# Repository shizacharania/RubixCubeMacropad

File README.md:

# RubixCubeMacropad

a fun project i built out over a weekend - learned how to make a PCB through kicad + made a rubix cube enclosure that has a three part assembly, with the pieces being precisely located + designed firmware for the macropad through KMK!

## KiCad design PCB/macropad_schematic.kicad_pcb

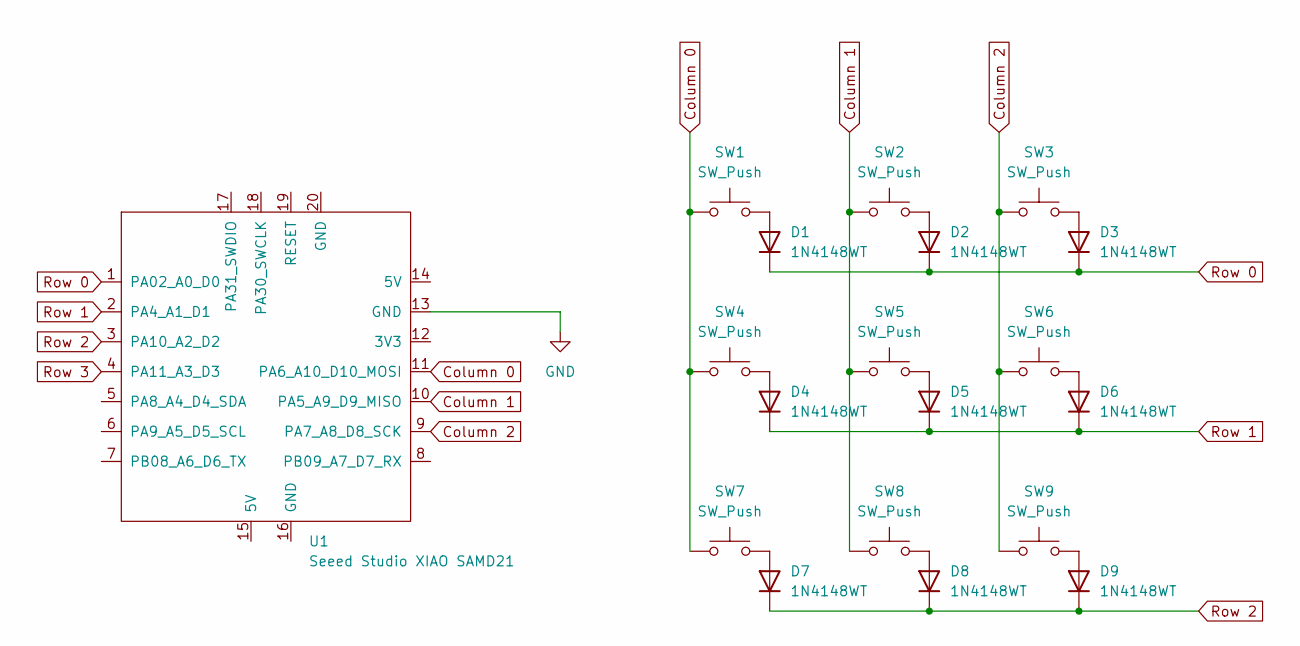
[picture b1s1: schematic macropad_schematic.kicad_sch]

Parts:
D1, D2, D3, D4, D5, D6, D7, D8, D9: 1N4148WT; D_SOD-523
SW1, SW2, SW3, SW4, SW5, SW6, SW7, SW8, SW9: SW_Push; SW_Cherry_MX_1.00u_PCB
U1: Seeed Studio XIAO SAMD21; XIAO-RP2040-SMD

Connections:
Column 0: SW1.1, SW4.1, SW7.1, U1.11 (PA6_A10_D10_MOSI)
Column 1: SW2.1, SW5.1, SW8.1, U1.10 (PA5_A9_D9_MISO)
Column 2: SW3.1, SW6.1, SW9.1, U1.9 (PA7_A8_D8_SCK)
GND: U1.13 (GND)
unnamed: D1.2 (A), SW1.2
unnamed: D2.2 (A), SW2.2
unnamed: D3.2 (A), SW3.2
unnamed: D4.2 (A), SW4.2
unnamed: D5.2 (A), SW5.2
unnamed: D6.2 (A), SW6.2
unnamed: D7.2 (A), SW7.2
unnamed: D8.2 (A), SW8.2
unnamed: D9.2 (A), SW9.2
RES_OUTPUT_A: U1.7 (PB08_A6_D6_TX)
RES_OUTPUT_B: U1.8 (PB09_A7_D7_RX)
Row 0: D1.1 (K), D2.1 (K), D3.1 (K), U1.1 (PA02_A0_D0)
Row 1: D4.1 (K), D5.1 (K), D6.1 (K), U1.2 (PA4_A1_D1)
Row 2: D7.1 (K), D8.1 (K), D9.1 (K), U1.3 (PA10_A2_D2)
Row 3: U1.4 (PA11_A3_D3)

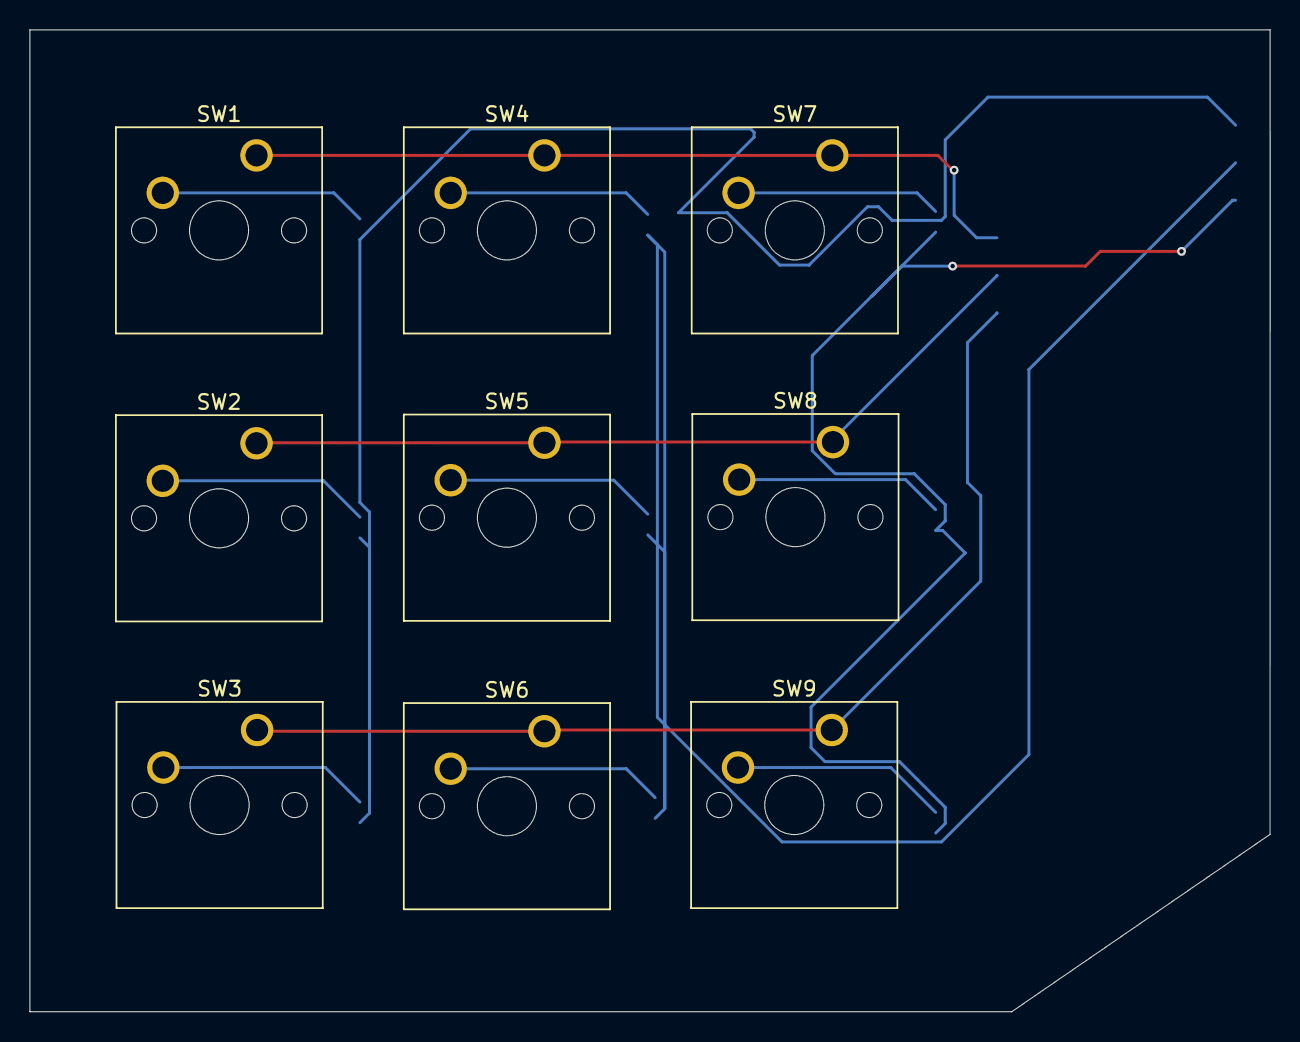
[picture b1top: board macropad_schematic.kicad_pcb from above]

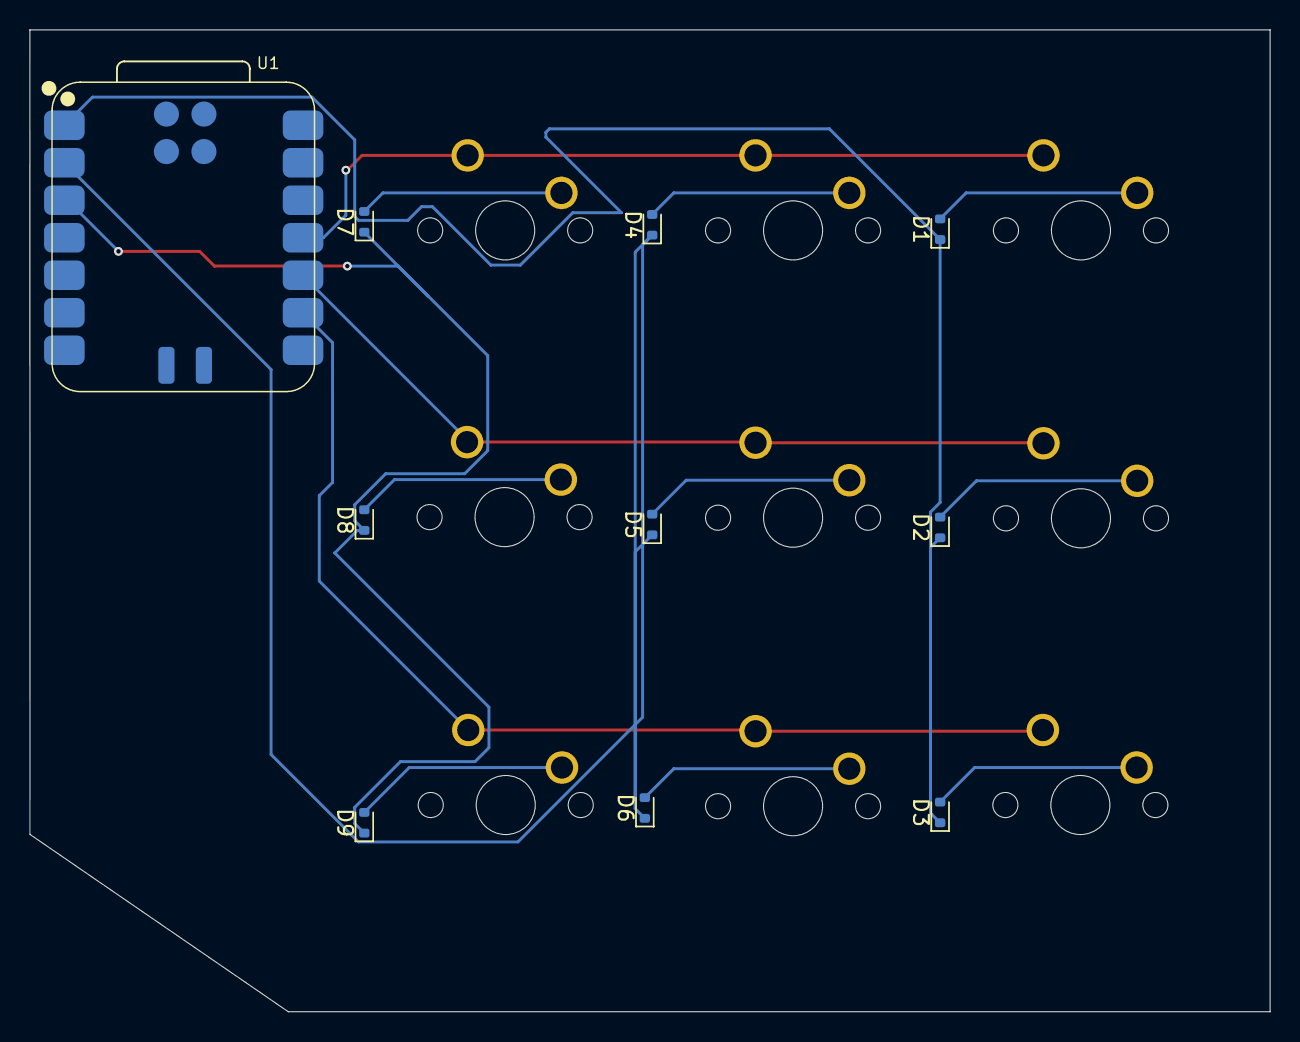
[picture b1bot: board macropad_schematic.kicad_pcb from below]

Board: 2 copper layers, 84.0 x 66.5 mm, 19 parts (10 on the bottom side), 15 nets.

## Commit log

2024-10-22 Create a
2024-10-22 added cad files
2024-10-22 Create Firmware folder
2024-10-22 step files for PCB components
2024-10-22 created folder for pcb files
2024-10-22 added pcb files
2024-10-28 give main.py updated solidworks commands
2024-10-28 add macropad - part1.stl
2024-10-28 remove CAD/case/macropad - part1.stl
2024-10-28 Create -
2024-10-28 add gerber files
2024-10-28 deleted empty gerber file
